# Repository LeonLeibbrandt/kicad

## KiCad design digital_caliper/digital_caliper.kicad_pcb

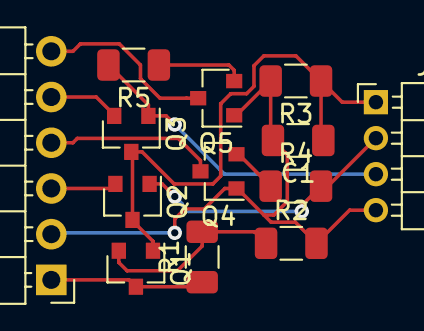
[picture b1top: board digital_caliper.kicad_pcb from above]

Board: 2 copper layers, 13 parts (0 on the bottom side), 12 nets.

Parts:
C1: 10u; C_1206_3216Metric
J1: Conn_01x06; PinHeader_1x06_P2.54mm_Horizontal
J2: Conn_01x04_Male; PinHeader_1x04_P2.00mm_Horizontal
Q1, Q4, Q5: 2N3904; SOT-23
Q2, Q3: 2N7000; SOT-23
R1: 120k; R_1206_3216Metric
R2, R3, R4, R5: 100k; R_1206_3216Metric

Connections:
GNDREF: C1.2, J1.2, J2.4, Q4.1, Q5.1, R2.2, R3.2
unnamed: C1.1, J2.1, Q1.1, Q2.3, Q3.3, R3.1
unnamed: J1.1, Q1.3, R1.1
unnamed: J1.3, Q2.2
unnamed: J1.4, Q4.3
unnamed: J1.5, Q3.2
unnamed: J1.6, Q5.3
unnamed: J2.2, Q2.1, R4.2
unnamed: J2.3, Q3.1, R5.2
unnamed: Q1.2, R1.2, R2.1
unnamed: Q4.2, R4.1
unnamed: Q5.2, R5.1

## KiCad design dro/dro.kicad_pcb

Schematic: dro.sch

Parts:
A1: Maple_Mini
J1: Barrel_Jack; BarrelJack_CUI_PJ-036AH-SMT_Horizontal
J2, J3, J4: Conn_01x04_Male; Hirose_DF13-04P-1.25DSA_1x04_P1.25mm_Vertical
U1: TSR_1-2433; Converter_DCDC_TRACO_TSR-1_THT
U2, U3: TXB0104D; SOIC-14_3.9x8.7mm_P1.27mm
U4: TSR_1-2415; Converter_DCDC_TRACO_TSR-1_THT

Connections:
unnamed: A1.1, U1.3 (Vout), U2.1, U3.1
unnamed: A1.2, J1.2, J2.4, J3.4, J4.4, U1.2 (GND), U2.7, U3.7, U4.2 (GND)
unnamed: A1.6, U2.2
unnamed: A1.7, U2.3
unnamed: A1.8, U2.4
unnamed: A1.9, U2.5
unnamed: A1.10, U3.2
unnamed: A1.11, U3.3
unnamed: A1.12, U3.4
unnamed: A1.13, U3.5
unnamed: J1.1, U1.1 (Vin), U4.1 (Vin)
unnamed: J2.1, J3.1, J4.1, U2.14, U3.14, U4.3 (Vout)
unnamed: J2.2, U2.13
unnamed: J2.3, U2.12
unnamed: J3.2, U2.11
unnamed: J3.3, U2.9, U2.10
unnamed: J4.2, U3.13
unnamed: J4.3, U3.12

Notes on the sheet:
12V IN
Licensed under a Creative Commons Attribution-Share-Alike Unported License. See creativecommons.org/licenses/by-sa/4.0/
Reference designs are provided "AS IS" and "WITH ALL FAULTS".
The author(s) disclaims all other warranties express or implied,
regarding this product, including but not limited to, any implied warranties of
merchantibility or fitness for any particular application.
The author(s) may make changes to specifications and product
descriptions at any time, without notice.

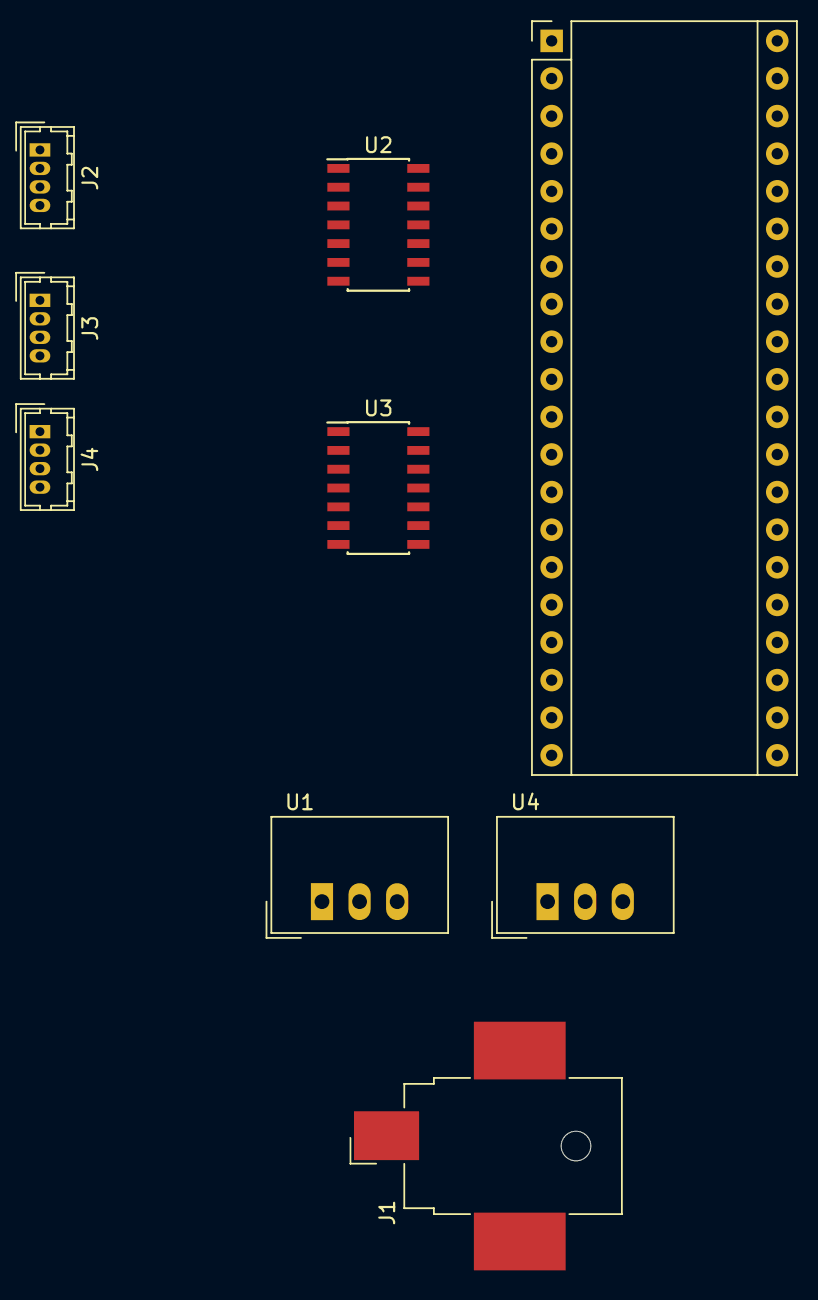
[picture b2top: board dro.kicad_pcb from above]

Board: 2 copper layers, 9 parts (0 on the bottom side), 18 nets, no tracks yet.

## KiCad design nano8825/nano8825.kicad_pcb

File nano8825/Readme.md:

# Nano8825 #

This is a little breakout board for [grbl](https://github.com/gnea/grbl) with a [Arduino Nano V3](https://store.arduino.cc/arduino-nano) and three [DRV8825 Stepper Motor Driver Carrier Boards](https://www.pololu.com/product/2133). I had to change some of the pin definitions for grbl (all still complies with being on the same port) to make the PC Board layout only a single sided board.

The design was made using [KiCad](http://kicad-pcb.org/) specifically with [Version 5](https://launchpad.net/~js-reynaud/+archive/ubuntu/kicad-5) which is still in development.

I have included all the changes needed in the cpu_map.h file as well as a compiled grbl with these changes.

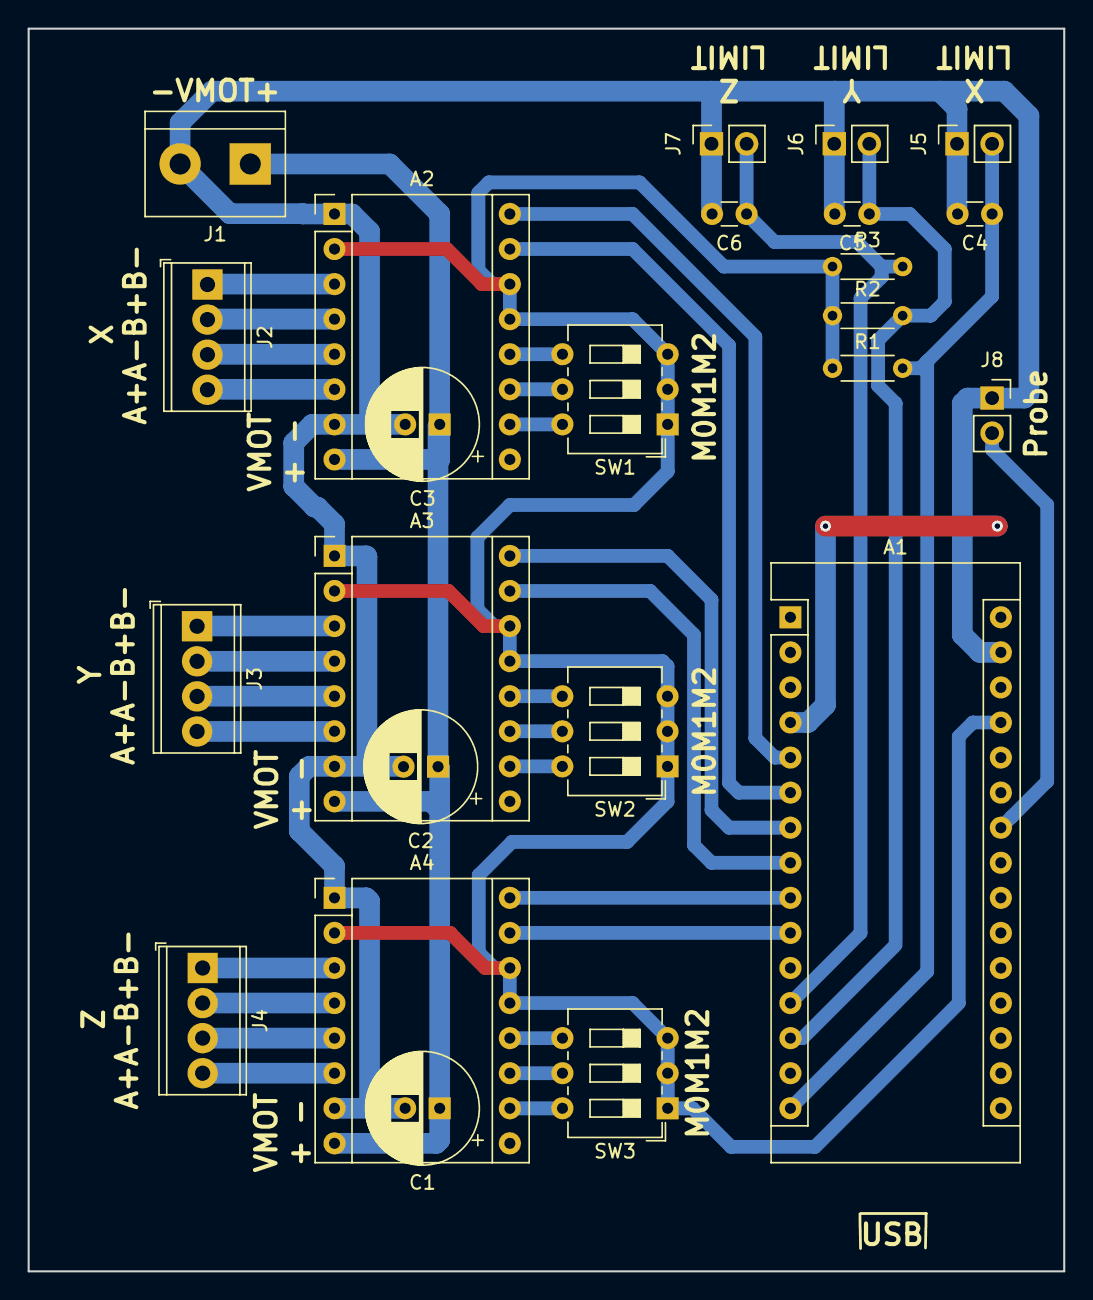
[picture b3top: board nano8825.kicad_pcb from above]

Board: 2 copper layers, 75.0 x 90.0 mm, 24 parts (0 on the bottom side), 34 nets.

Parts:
A1: Arduino_Nano_v3.x; Arduino_Nano
A2, A3, A4: Pololu_Breakout_DRV8825; Pololu_Breakout-16_15.2x20.3mm
C1, C2, C3: 100u; CP_Radial_D8.0mm_P2.50mm
C4, C5, C6: 100n; C_Disc_D3.0mm_W1.6mm_P2.50mm
J1: Conn_01x02; TerminalBlock_bornier-2_P5.08mm
J2, J3, J4: Conn_01x04; TerminalBlock_Phoenix_MPT-0,5-4-2.54_1x04_P2.54mm_Horizontal
J5, J6, J7: Conn_01x02; PinSocket_1x02_P2.54mm_Vertical
J8: Conn_01x02_Female; PinSocket_1x02_P2.54mm_Vertical
R1, R2, R3: 4k7; R_Axial_DIN0204_L3.6mm_D1.6mm_P5.08mm_Horizontal
SW1, SW2, SW3: SW_DIP_x03; SW_DIP_SPSTx03_Slide_6.7x9.18mm_W7.62mm_P2.54mm_LowProfile

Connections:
unnamed: A1.5, A2.16
unnamed: A1.6, A2.15
unnamed: A1.7, A3.16
unnamed: A1.8, A3.15
unnamed: A1.9, A4.16
unnamed: A1.10, A4.15
unnamed: A1.12, C6.1, J7.2, R3.2
unnamed: A1.13, C5.1, J6.2, R2.2
unnamed: A1.15, C4.1, J5.2, R1.2
unnamed: A1.24, J8.2
unnamed: A1.27, A2.2, A2.13, A2.14, A3.2, A3.13, A3.14, A4.2, A4.13, A4.14, R1.1, R2.1, R3.1, SW1.1, SW1.2, SW1.3, SW2.1, SW2.2, SW2.3, SW3.1, SW3.2, SW3.3
unnamed: A1.4, A1.29, A2.1, A2.7, A3.1, A3.7, A4.1, A4.7, C1.2, C2.2, C3.2, C4.2, C5.2, C6.2, J1.2, J5.1, J6.1, J7.1, J8.1
unnamed: A2.3, J2.1
unnamed: A2.4, J2.2
unnamed: A2.5, J2.3
unnamed: A2.6, J2.4
unnamed: A2.8, A3.8, A4.8, C1.1, C2.1, C3.1, J1.1
unnamed: A2.10, SW1.6
unnamed: A2.11, SW1.5
unnamed: A2.12, SW1.4
unnamed: A3.3, J3.1
unnamed: A3.4, J3.2
unnamed: A3.5, J3.3
unnamed: A3.6, J3.4
unnamed: A3.10, SW2.6
unnamed: A3.11, SW2.5
unnamed: A3.12, SW2.4
unnamed: A4.3, J4.1
unnamed: A4.4, J4.2
unnamed: A4.5, J4.3
unnamed: A4.6, J4.4
unnamed: A4.10, SW3.6
unnamed: A4.11, SW3.5
unnamed: A4.12, SW3.4

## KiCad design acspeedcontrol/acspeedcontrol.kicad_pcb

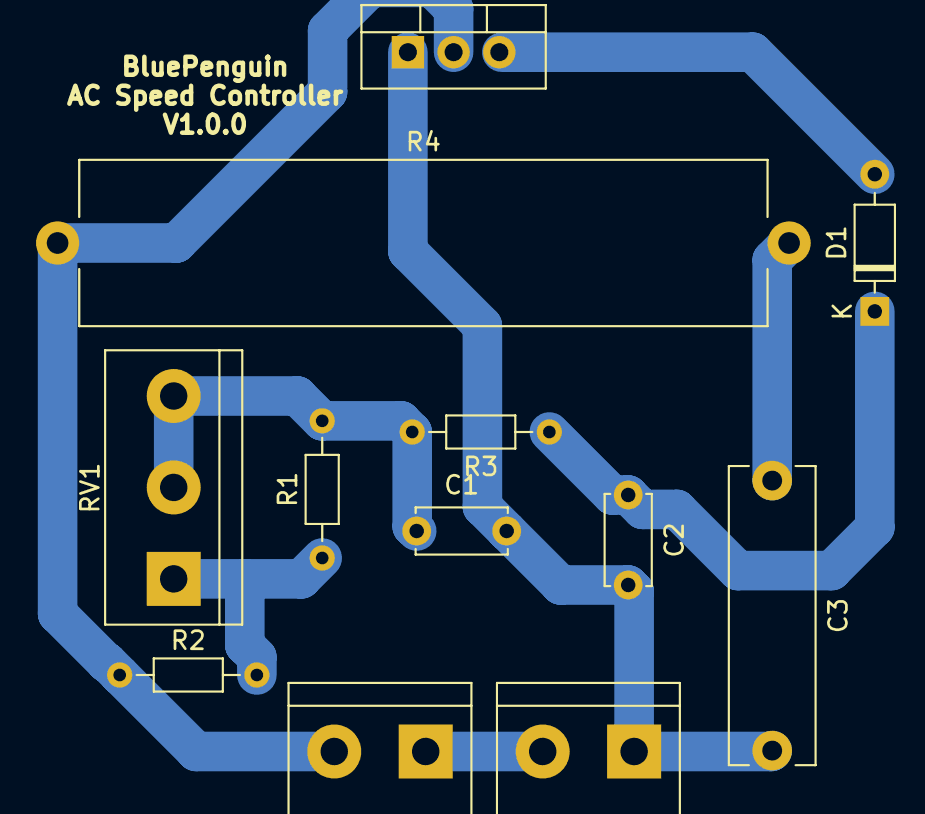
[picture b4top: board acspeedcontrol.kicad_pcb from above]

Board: 2 copper layers, 12 parts (0 on the bottom side), 8 nets.

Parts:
C1, C2: 22n; C_Disc_D5.0mm_W2.5mm_P5.00mm
C3: 33n; C_Rect_L16.5mm_W4.7mm_P15.00mm_MKT
D1: DIAC; D_DO-35_SOD27_P7.62mm_Horizontal
D2: Q_TRIAC_A1A2G; TO-220-3_Vertical
J1, J2: Conn_01x02; TerminalBlock_bornier-2_P5.08mm
R1: 3M9; R_Axial_DIN0204_L3.6mm_D1.6mm_P7.62mm_Horizontal
R2: 56k; R_Axial_DIN0204_L3.6mm_D1.6mm_P7.62mm_Horizontal
R3: 10k; R_Axial_DIN0204_L3.6mm_D1.6mm_P7.62mm_Horizontal
R4: 100 7W; R_Axial_Power_L38.0mm_W9.0mm_P40.64mm
RV1: 1M; TerminalBlock_bornier-3_P5.08mm

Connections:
unnamed: C1.1, R1.2, R3.2, RV1.2, RV1.3
unnamed: C1.2, C2.2, C3.2, D2.1, J2.1
unnamed: C2.1, D1.1, R3.1
unnamed: C3.1, R4.2
unnamed: D1.2, D2.3
unnamed: D2.2, J1.2, R2.1, R4.1
unnamed: J1.1, J2.2
unnamed: R1.1, R2.2, RV1.1

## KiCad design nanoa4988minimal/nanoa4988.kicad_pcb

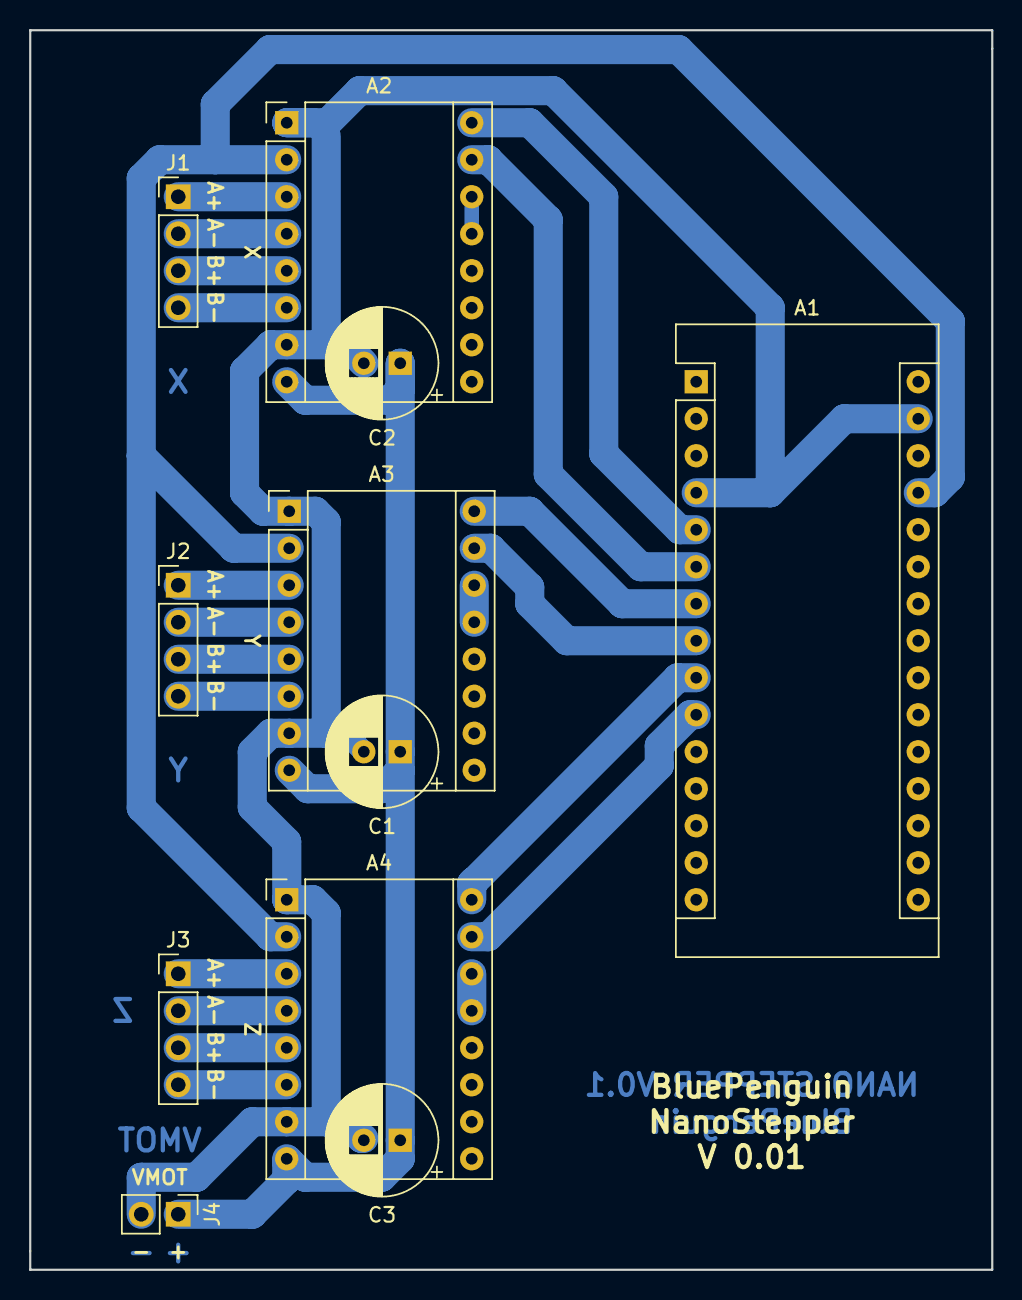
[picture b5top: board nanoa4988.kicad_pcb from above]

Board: 2 copper layers, 66.0 x 85.1 mm, 11 parts (0 on the bottom side), 24 nets.

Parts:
A1: Arduino_Nano_v3.x; Arduino_Nano
A2, A3, A4: Pololu_Breakout_A4988; Pololu_Breakout-16_15.2x20.3mm
C1, C2, C3: CP1; CP_Radial_D7.5mm_P2.50mm
J1, J2, J3: Conn_01x04; PinHeader_1x04_P2.54mm_Vertical
J4: Conn_01x02; PinHeader_1x02_P2.54mm_Vertical

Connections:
unnamed: A1.5, A2.16
unnamed: A1.6, A2.15
unnamed: A1.7, A3.16
unnamed: A1.8, A3.15
unnamed: A1.9, A4.16
unnamed: A1.10, A4.15
unnamed: A1.27, A2.2, A3.2, A4.2
unnamed: A1.4, A1.29, A2.1, A2.7, A3.1, A3.7, A4.1, A4.7, C1.2, C2.2, C3.2, J4.2
unnamed: A2.3, J1.1
unnamed: A2.4, J1.2
unnamed: A2.5, J1.3
unnamed: A2.6, J1.4
unnamed: A2.8, A3.8, A4.8, C1.1, C2.1, C3.1, J4.1
unnamed: A2.13, A2.14
unnamed: A3.3, J2.1
unnamed: A3.4, J2.2
unnamed: A3.5, J2.3
unnamed: A3.6, J2.4
unnamed: A3.13, A3.14
unnamed: A4.3, J3.1
unnamed: A4.4, J3.2
unnamed: A4.5, J3.3
unnamed: A4.6, J3.4
unnamed: A4.13, A4.14

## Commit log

2018-04-09 First Upload
2018-04-09 Fix dir layout
2018-04-09 Further Cleanup
2018-04-14 Added limit and probe connectors
2018-04-14 Cleaned directories
2018-04-14 Renamed files
2018-04-14 Added Readme
2018-04-14 Added references to Readme file
2018-04-29 Added Output for nano8825 board
2018-05-25 Updated some footprints
2018-05-25 Updated Outputs
2018-07-22 Added Caliper and updated drv8825 board
2018-08-24 Updated Layout
2018-10-03 Added FAULT line to force fast decay
2018-10-18 Added Fourt Axis
2019-03-24 Added DRO
